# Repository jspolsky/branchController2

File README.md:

branchController
================

The Branch Controller is a small hardware board based on the [Teensy 3.2 development board](https://www.pjrc.com/store/teensy32.html) to allow it to control up to 8 separate pixel-addressible LED strips.

Although it can be used standalone to send its own patterns to the light strips, it really shines when connected, over ethernet, to a network. That allows you to generate the patterns on a computer (say, with a high powered graphics card) and send them to one or more Branch Controllers. In particular you can drive a lot more LEDs than any single controller can drive by using multiple Branch Controllers.

It is designed for WS2812b-style LED strips, with a single wire protocol. These are what Adafruit calls "NeoPixels".

Personally I like to use the WS2815 variant which runs on 12 volts and has a backup wire allowing any single pixel to fail. 

Branch Controller does *not* handle APA102c-type strips, which use a two wire protocol consisting of both the signal and a clock.

Features:

* Supports up to 4400 pixels (550 per strip) at a frame rate of 60 Hz, the theoretical limit of the protocol

* Ethernet control. Connects to an ethernet network to receive pixel data over TCP/IP. This allows you to use many branch controllers controlled from a single PC

* 128x32 OLED display for diagnostics and network configuration

* IR sensor allows you to use an IR remote control for basic controls

Basic Operation
---------------

By default branchController assumes you have 8 strips of 550 pixels each. You can operate a single branchController with a 44 button IR remote control like this one:

The brightness and color buttons work out of the box so you can use your branch controller to create basic solid colors. 

Use the On/Off button on the remote to turn off the LEDs. When you press OFF, any changes you have made to the state of the branchController is saved to EEPROM so that it will come back in the same state when you power up. *If you don't press off, the state is never saved*.

The DIY1-6 buttons are reserved for internal test patterns and chases. You can edit the code for these to provide something that is a good backup if your PC or network fails.

DIY1 shows a test pattern where the first pixel is brown on the first strip, the first two pixels are brown on the second strip, etc. This is useful for making sure you have the 8 strips hooked up in the right order.

Network Operation
-----------------

You can connect your branchController to a LAN using the built-in ethernet port and control it from any kind of computer that speaks TCP/IP.

When branchController starts up, it will look for a DHCP server and try to get an IP address and network configuration. If that works it will show you the IP address on the screen.

Every branch controller has a unique MAC address which will never change, so you can configure your DHCP server to always hand out the same IP address to the same branch controller, which makes it easier to sort out multiple branch controllers.

If you would like to use a static IP address:

* Start up the branch controller once using DHCP
* Connect to the web server running at the IP address that you see on the OLED display
* Check the "static IP" box and enter the IP address you want to use. Click submit
* Restart the branch controller. From now on it will use your static IP address.

Web-based Hardware Configuration
--------------------------------

If you don't like the default configuration, you can use a web browser to connect to your
branchController and modify some things:

* the maximum power that LEDs will be allowed to consume (in milliwatts). If the total power budget is exceeded, all LEDs will be dimmed equally.
* the RGB order in your LED strips (some strips expect RGB, others expect GRB). Use the "red", "green", and "blue" buttons to diagnose incorrect RGB order.
* the color correction you want applied to all output, as a six digit hex RGB value
* the color temperature you want applied to all output, as a six digit hex RGB value
* the overall brightness of the LEDs, on a scale from 0 (off) to 255 (full). This can
  also be adjusted with an IR remote
* whether to use a static IP address 

See http://fastled.io/docs/3.1/group___color_enums.html for options for color correction and 
color temperature.

Open Pixel Control
------------------

If branchController successfully gets on the Internet, it will listen for TCP connections on port 7890, where it will receive data sent to it using the Open Pixel Control format, documented [here](http://openpixelcontrol.org/). You can use Christopher Schardt's app [L.E.D. Lab](https://apps.apple.com/us/app/l-e-d-lab/id832042156) for iPhone or iPad to send cool animations -- all you need to do is set up the controller as if it were a FadeCandy controller.

We use TCP and not UDP for Open Pixel Control. The w5500 ethernet chip used in this design has a tiny buffer and will lose UDP packets if they are sent too fast. TCP solves this problem.

About the project
-----------------

This code was built using PlatformIO, an open source platform for embedded development which is a zillion times better than using the Arduino IDE. You will still need Teensyduino to flash the Teensy. For more about the research behind this project, follow my blog, [BlinkyLights](https://blinkylights.blog/).

Want to build one?
-------------------
* The gerber directory has gerber and drill files so you can order PCBs.
* This [BOM](https://octopart.com/bom-tool/tv6ZDeDl) lists the parts you need.
* The PCB is designed to be mounted in a Polycase SK-16-03 if you want a weatherproof enclosure

Next Up
-------

Recently implemented:
- [X] Static IP address
- [X] Faster brightness adjust

These features are planned REAL SOON NOW:
- [ ] Improve power limiting feature by showing stats on display for diagnosis
- [ ] "Count Pixels" mode
- [ ] Investigate temporal dithering - it's not really happening. 
- [ ] Internet cable disconnected / reconnected
- [ ] Better built-in (DIY1-6) displays maybe
- [ ] Support remote control Play/Pause button for internal DIY1-6 displays
- [ ] Either implement gamma correction or stop pretending

Ideas for future improvements:
- [ ] New hardware design with ESP32 and logic shifters to handle way more LEDs
- [ ] TouchDesigner support
- [ ] DMX/ArtNet bridge mode
- [ ] Multicast DNS (mDNS) and service discovery (DNS-SD)
      try https://github.com/TrippyLighting/EthernetBonjour

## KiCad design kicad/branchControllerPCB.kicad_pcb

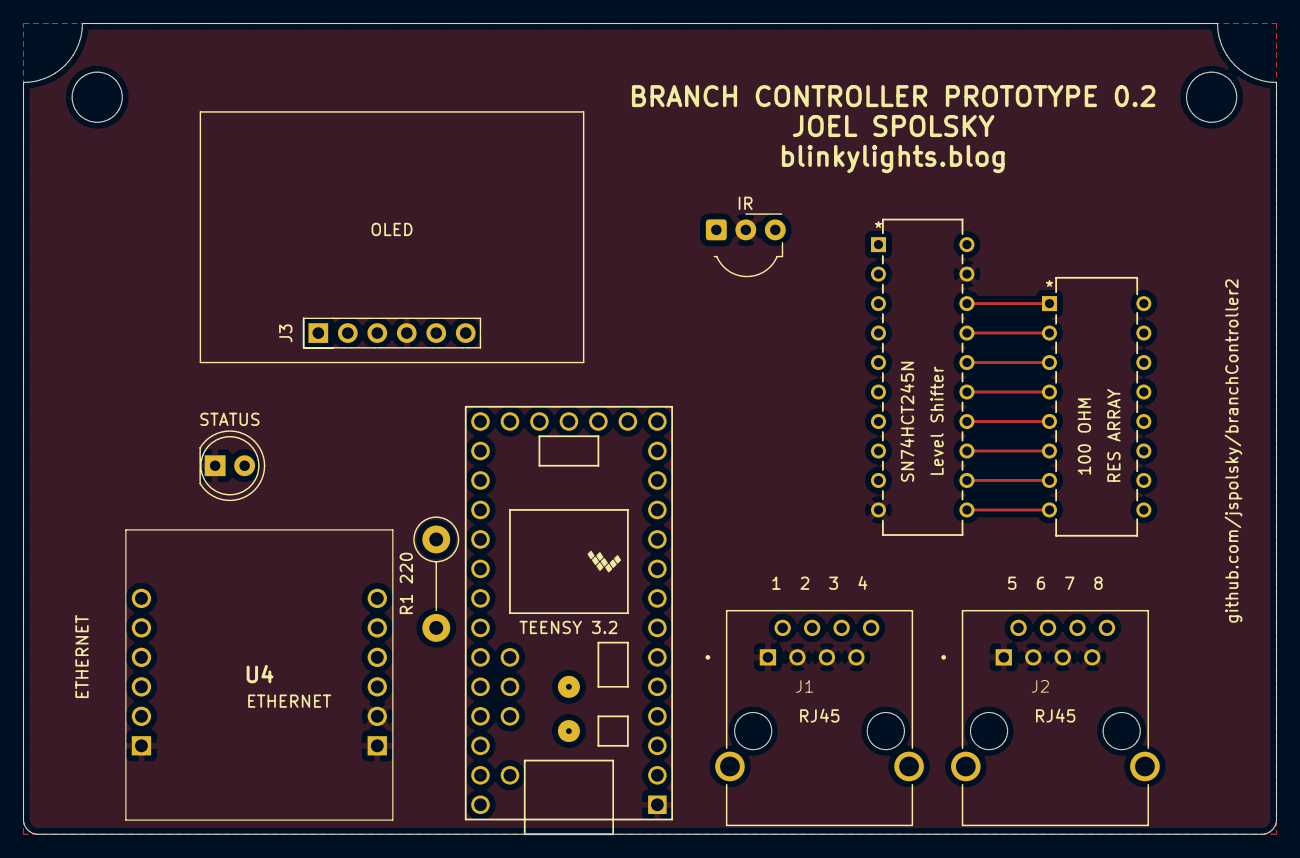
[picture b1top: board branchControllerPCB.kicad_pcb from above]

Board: 4 copper layers, 107.9 x 69.9 mm, 10 parts (0 on the bottom side), 36 nets.

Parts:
100 OHM: RES ARRAY; 4116R-1-101LF
IR: TSOP34438 IR SENSOR; Vishay_MOLD-3Pin
J1, J2: RJ45 AE10388-ND; ASSMANN_A-2004-1-4-LP-N-R
J3: Adafruit 4400 32x128 OLED; AdaFruit4400LED
R1 220: 220 Ω; R_Axial_DIN0411_L9.9mm_D3.6mm_P7.62mm_Vertical
SN74HCT245N: Level Shifter; SN74HCT245N
STATUS: Grn Status LED; LED_D5.0mm
TEENSY 3.2: Teensy3.2; Teensy30_31_32_LC
U4: WIZ850io Ethernet; WIZ850io

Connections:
+3V3: IR.3, SN74HCT245N.1, TEENSY 3.2.31, U4.8, U4.9
+5V: J3.VIN, SN74HCT245N.20, TEENSY 3.2.33
/I2CSCL: J3.SCL, TEENSY 3.2.26
/I2CSDA: J3.SDA, TEENSY 3.2.25
/IR: IR.1, TEENSY 3.2.5
/MISO: TEENSY 3.2.14, U4.12
/MOSI: TEENSY 3.2.13, U4.3
/SCLK: TEENSY 3.2.20, U4.4
/SCN: TEENSY 3.2.12, U4.5
/STR1: SN74HCT245N.2, TEENSY 3.2.4
/STR2: SN74HCT245N.3, TEENSY 3.2.21
/STR3: SN74HCT245N.4, TEENSY 3.2.9
/STR4: SN74HCT245N.5, TEENSY 3.2.10
/STR5: SN74HCT245N.6, TEENSY 3.2.8
/STR6: SN74HCT245N.7, TEENSY 3.2.27
/STR7: SN74HCT245N.8, TEENSY 3.2.28
/STR8: SN74HCT245N.9, TEENSY 3.2.7
GND: IR.2, J1.1, J1.3, J1.5, J1.7, J2.1, J2.3, J2.5, J2.7, J3.GND, SN74HCT245N.10, SN74HCT245N.19, STATUS.1, TEENSY 3.2.1, U4.1, U4.2, U4.7
unnamed: R1 220.1, STATUS.2
unnamed: 100 OHM.16, J1.2
unnamed: 100 OHM.15, J1.4
unnamed: 100 OHM.14, J1.6
unnamed: 100 OHM.13, J1.8
unnamed: 100 OHM.12, J2.2
unnamed: 100 OHM.11, J2.4
unnamed: 100 OHM.10, J2.6
unnamed: 100 OHM.9, J2.8
unnamed: R1 220.2, TEENSY 3.2.30
unnamed: 100 OHM.1, SN74HCT245N.18
unnamed: 100 OHM.2, SN74HCT245N.17
unnamed: 100 OHM.3, SN74HCT245N.16
unnamed: 100 OHM.4, SN74HCT245N.15
unnamed: 100 OHM.5, SN74HCT245N.14
unnamed: 100 OHM.6, SN74HCT245N.13
unnamed: 100 OHM.7, SN74HCT245N.12
unnamed: 100 OHM.8, SN74HCT245N.11

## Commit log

2019-12-16 Start with generic BLINK code!
2019-12-16 Structuring the code in a sustainable way
2019-12-16 better readme
2019-12-16 distinctive heartbeat led shows our code is running
2019-12-17 Utility debugging function. Debug and Release mode
2019-12-17 ignore workspace
2019-12-17 not gonna travis.ci
2019-12-17 Minor cleanups to debug printing code
2019-12-17 rename main file
2019-12-17 Incorporated rudimentary support for OLED display
2019-12-17 Rudimentary ethernet support; needs a lot of work!
2019-12-17 FastLED integrated (just running test patterns)
2019-12-18 unneeded delay
2019-12-19 Rudimentary support for Infrared Remote!
2019-12-19 some ambitious documentation
2019-12-19 support for solid color buttons on remote control
2019-12-19 documentation
2019-12-19 remember state on power off
2019-12-20 figured out how to get a Mac address from a Teensy
2019-12-20 clean up ethernet boot sequence
2019-12-20 fixed up display to show TCP status, AUTO to reconnect
2019-12-21 turn off display when OFF button is pressed
2019-12-22 Started creating schematic in KiCad
2019-12-22 finished the schematics in kicad
2019-12-22 finished designing prototype circuit board
2019-12-23 tweaks and improvements to PCB
2019-12-23 final kicad
2019-12-23 minor
2019-12-24 brightness control, frame rate report
2019-12-24 plans
2019-12-24 restructured ethernet code to be non-blocking
2019-12-24 initial implementation of Open Pixel Control
2019-12-24 yikes improve fps by a lot
2019-12-25 frame rate calc
2019-12-25 "todo" cleanup
2019-12-25 free memory monitoring
2019-12-25 stop telling me the fastled version number
2019-12-25 eliminated a lot of compiler warnings
2019-12-26 variables renamed
2019-12-26 experimental work to resize octows2811 controller
2019-12-26 working implementation of resizable controller
2019-12-26 finished resizable controller stuff
2019-12-26 gitignore
2019-12-27 improved OPC error handling
2019-12-27 not using this
2019-12-27 updated todo list
2019-12-27 We'll run a little web server on the side for configuration
2019-12-27 some nice refactoring
2019-12-27 WebServer is now non-blocking and pulls GET out
2019-12-27 typo
2019-12-27 show date and time
2019-12-28 Updated README. Implemented a basic web form
2020-01-02 BOM link
2020-01-02 a lot of progress on web server, but not done yet
2020-01-03 Finished implementing web server, including color
2020-01-03 fixed link to bom
2020-01-03 update todo list
2020-01-03 planned next moves
2020-01-03 gerber files ... UNTESTED!
2020-01-07 check the schematic in, in case it helps anyone
2020-01-09 Tweaked PCB dimensions
    No electrical changes
2020-01-21 some todo's before I forget
2020-01-22 todo updates
2020-01-22 Make the brightness adjustment knob feel smooth
2020-01-26 nope
2020-01-26 updated doc
2020-01-28 todos updated
2020-01-28 Wait 5s after last OPC msg before switching to default pattern
2020-01-28 reasonable UDP support. Needs some cleanup and optimization for real-world UDP
2020-01-28 better status message
2020-01-28 updates, doc 480 pix opc limitation
2020-01-28 udp-done!
2020-02-19 javascript test code
2020-02-22 Revert "todos updated"
    This reverts commit a11bc023fca70936e630f914bac5dd384534a3b9.
2020-02-22 Revert UDP support (everything back to a11bc02).
2020-02-22 Eliminate stutter when no OLED
2020-02-23 next up
2020-02-23 Static IP address assignment through web interface
2020-02-24 vs code junk
2020-03-01 launch.json should be gitignored

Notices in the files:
parts and their libraries:
Copyright 2016 Accelerated Designs. All rights reserved.
